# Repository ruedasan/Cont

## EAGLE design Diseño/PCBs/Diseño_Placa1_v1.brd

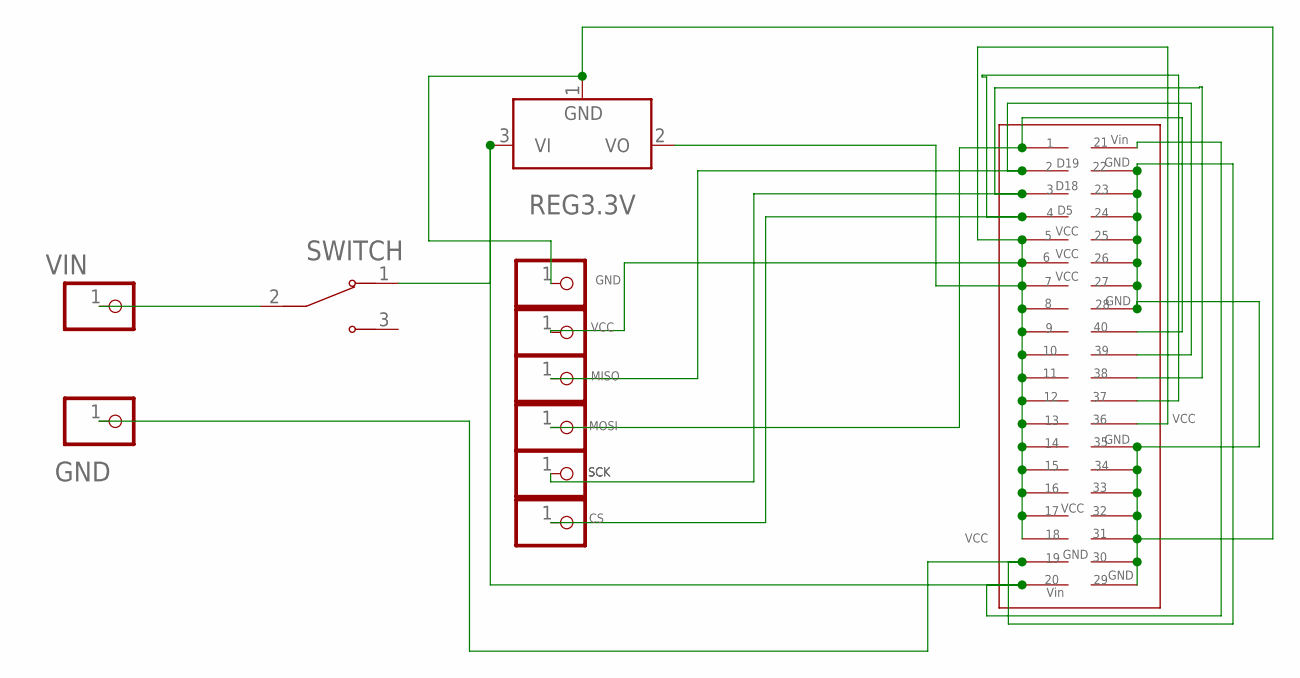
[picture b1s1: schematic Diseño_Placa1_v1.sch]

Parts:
GND: PINHD-1X1; 1X01
JP1: GND; 1X01
JP2: VCC; 1X01
JP3: MISO; 1X01
JP4: MOSI; 1X01
JP5: SCK; 1X01
JP6: CS; 1X01
REG3.3V: LD1117_TO220; TO220V
SWITCH: MINI-SPDT-SW; SW_MINI-SPDT-SW
U$1: PINHEADER
VIN: PINHD-1X1; 1X01

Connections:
unnamed: JP4.1, U$1.1, U$1.40
unnamed: SWITCH.2, VIN.1
unnamed: JP3.1, U$1.2, U$1.39
unnamed: JP5.1, U$1.3, U$1.38
unnamed: JP6.1, U$1.4, U$1.37
unnamed: GND.1, JP1.1, REG3.3V.1 (GND), U$1.19, U$1.22, U$1.23, U$1.24, U$1.25, U$1.26, U$1.27, U$1.28, U$1.29, U$1.30, U$1.31, U$1.32, U$1.33, U$1.34, U$1.35
unnamed: REG3.3V.3 (VI), SWITCH.1, U$1.20, U$1.21
unnamed: JP2.1, REG3.3V.2 (VO), U$1.5, U$1.6, U$1.7, U$1.8, U$1.9, U$1.10, U$1.11, U$1.12, U$1.13, U$1.14, U$1.15, U$1.16, U$1.17, U$1.18, U$1.36

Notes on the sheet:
D19
D18
GND
VCC
MISO
MOSI
SCK
Vin

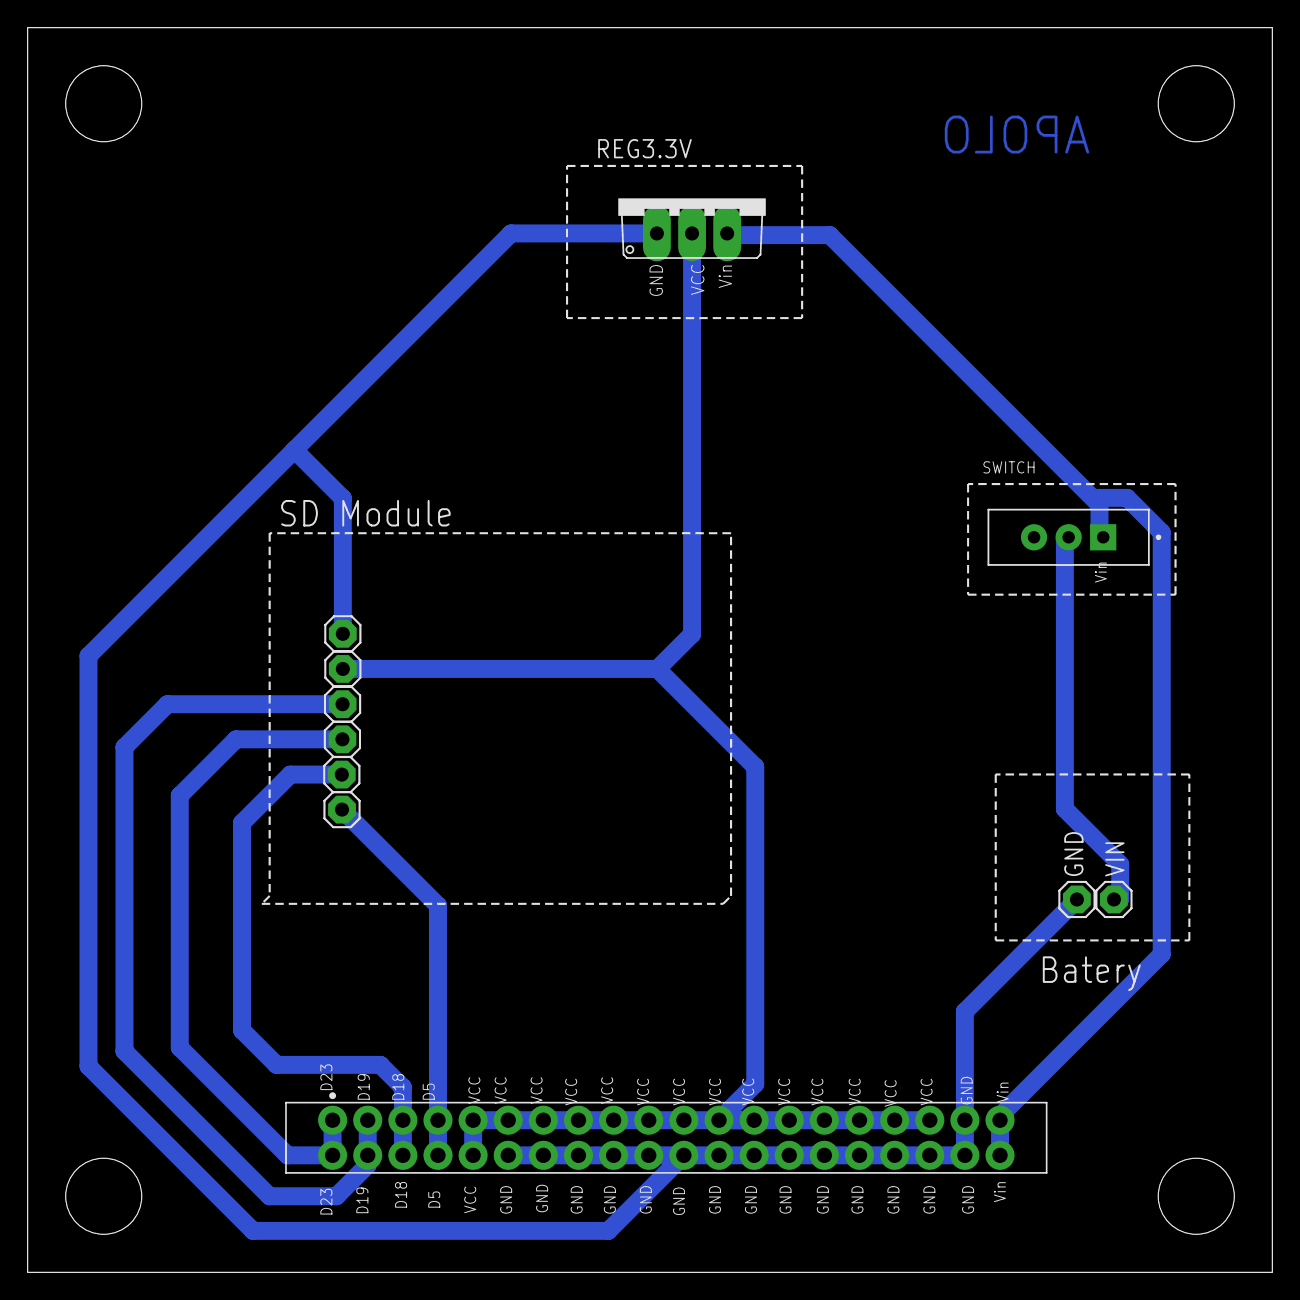
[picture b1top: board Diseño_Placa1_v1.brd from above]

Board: 2 copper layers, 90.0 x 90.0 mm, 11 parts (0 on the bottom side), 8 nets.

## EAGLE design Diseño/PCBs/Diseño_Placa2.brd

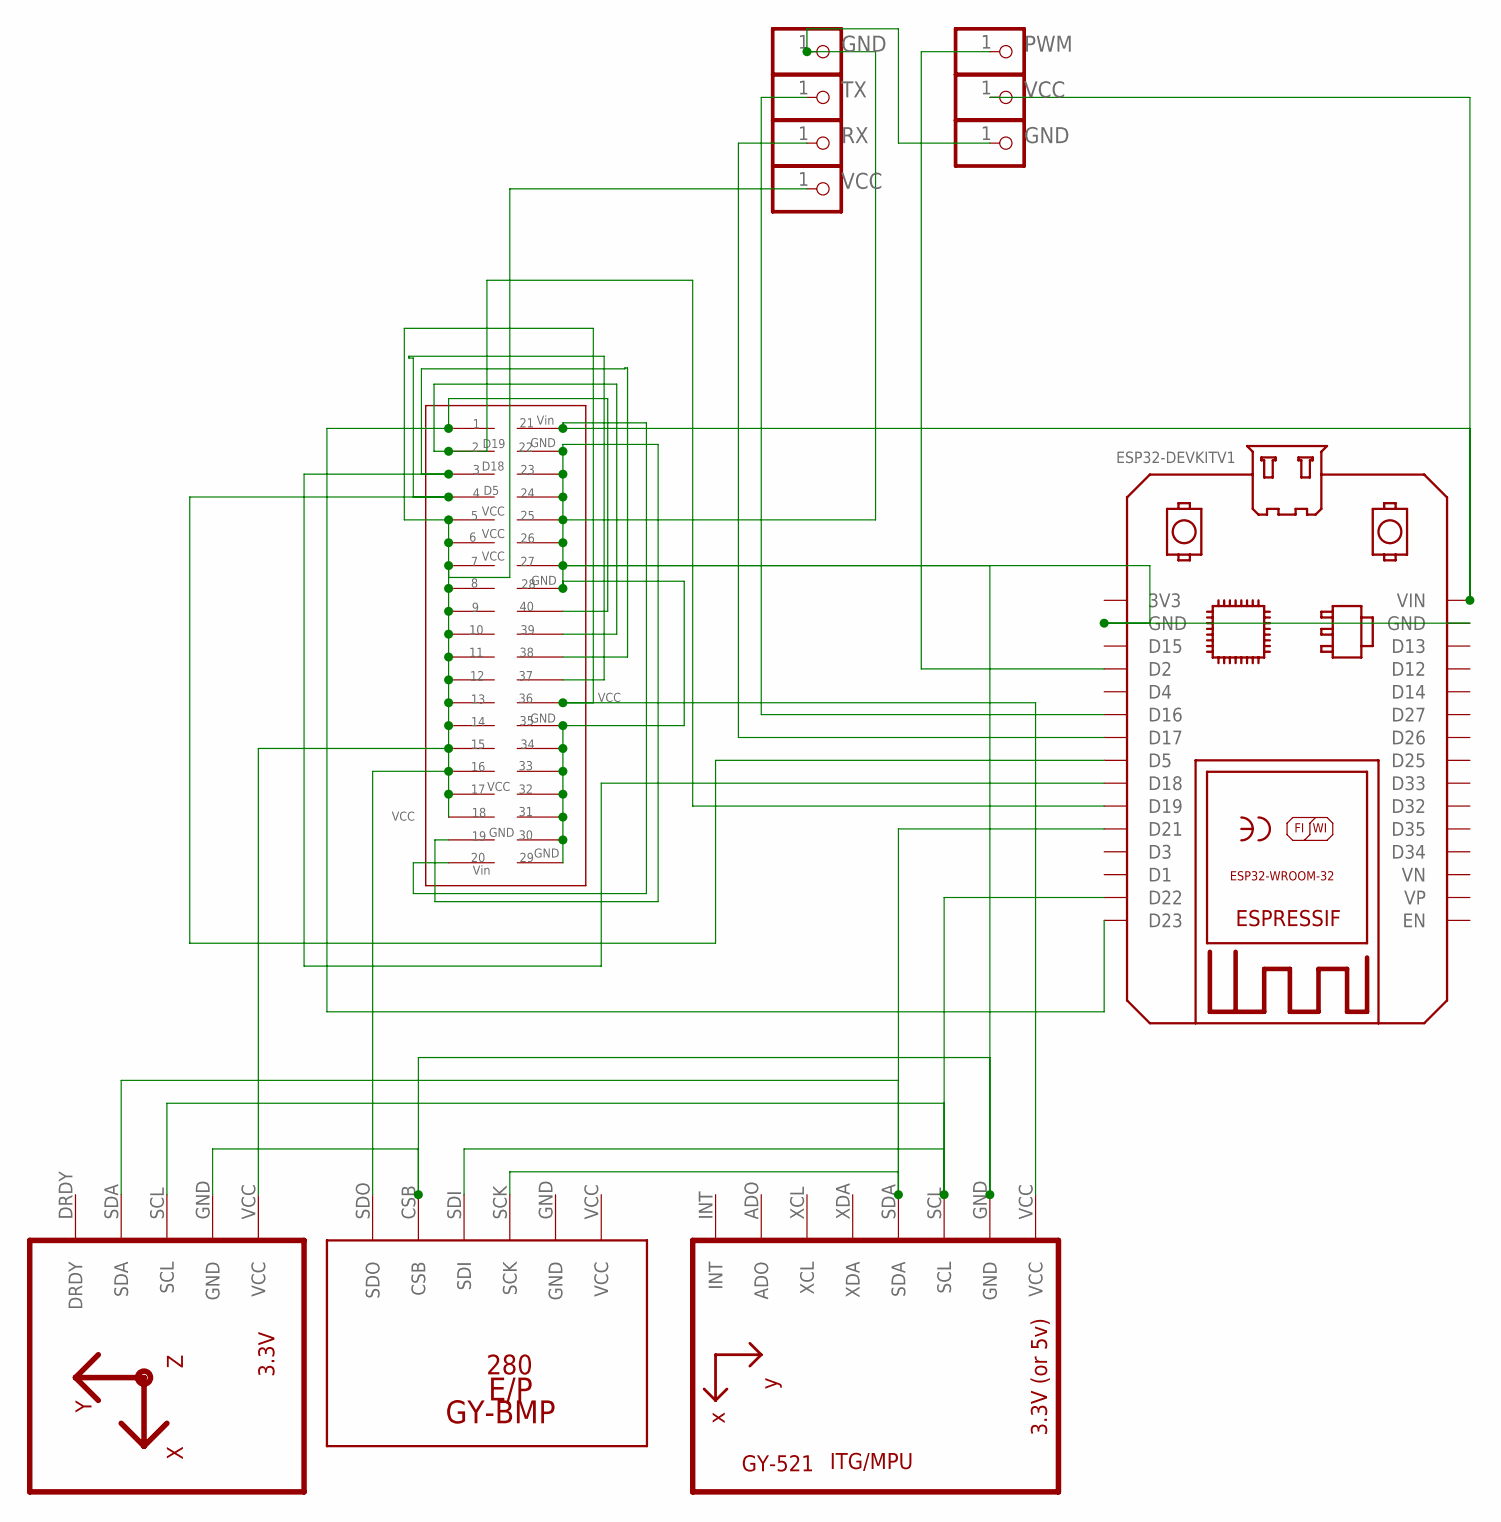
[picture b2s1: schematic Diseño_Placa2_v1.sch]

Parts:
3.3V: PWM; 1X01
3.3V3: GND; 1X01
3.3V4: VCC; 1X01
BOARD1: ESP32DEVKITV1; ESP32-DEVKITV1
GND: VCC; 1X01
GND3: TX; 1X01
GY-271: HMC5883LGY-271; GY-271
PWM: GND; 1X01
PWM3: RX; 1X01
U1: GY-521MPU6050; GY-521
U$1: GY-BPM280; GY-BMP280-FOOTPRINT
U$3: PINHEADER

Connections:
GND: 3.3V3.1, BOARD1.GND, BOARD1.GND@1 (GND), GY-271.GND, PWM.1, U1.GND, U$1.CSB, U$3.19, U$3.22, U$3.23, U$3.24, U$3.25, U$3.26, U$3.27, U$3.28, U$3.29, U$3.30, U$3.31, U$3.32, U$3.33, U$3.34, U$3.35
unnamed: BOARD1.D17, PWM3.1
unnamed: BOARD1.D16, GND3.1
unnamed: 3.3V.1, BOARD1.D2
unnamed: BOARD1.D22, GY-271.SCL, U1.SCL, U$1.SDI
unnamed: BOARD1.D21, GY-271.SDA, U1.SDA, U$1.SCK
unnamed: BOARD1.D23, U$3.1, U$3.40
unnamed: BOARD1.D19, U$3.2, U$3.39
unnamed: BOARD1.D18, U$3.3, U$3.38
unnamed: BOARD1.D5, U$3.4, U$3.37
unnamed: BOARD1.VIN, GND.1, U$3.20, U$3.21
unnamed: 3.3V4.1, GY-271.VCC, U1.VCC, U$1.SDO, U$3.5, U$3.6, U$3.7, U$3.8, U$3.9, U$3.10, U$3.11, U$3.12, U$3.13, U$3.14, U$3.15, U$3.16, U$3.17, U$3.18, U$3.36

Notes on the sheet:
D19
D18
VCC
Vin
GND

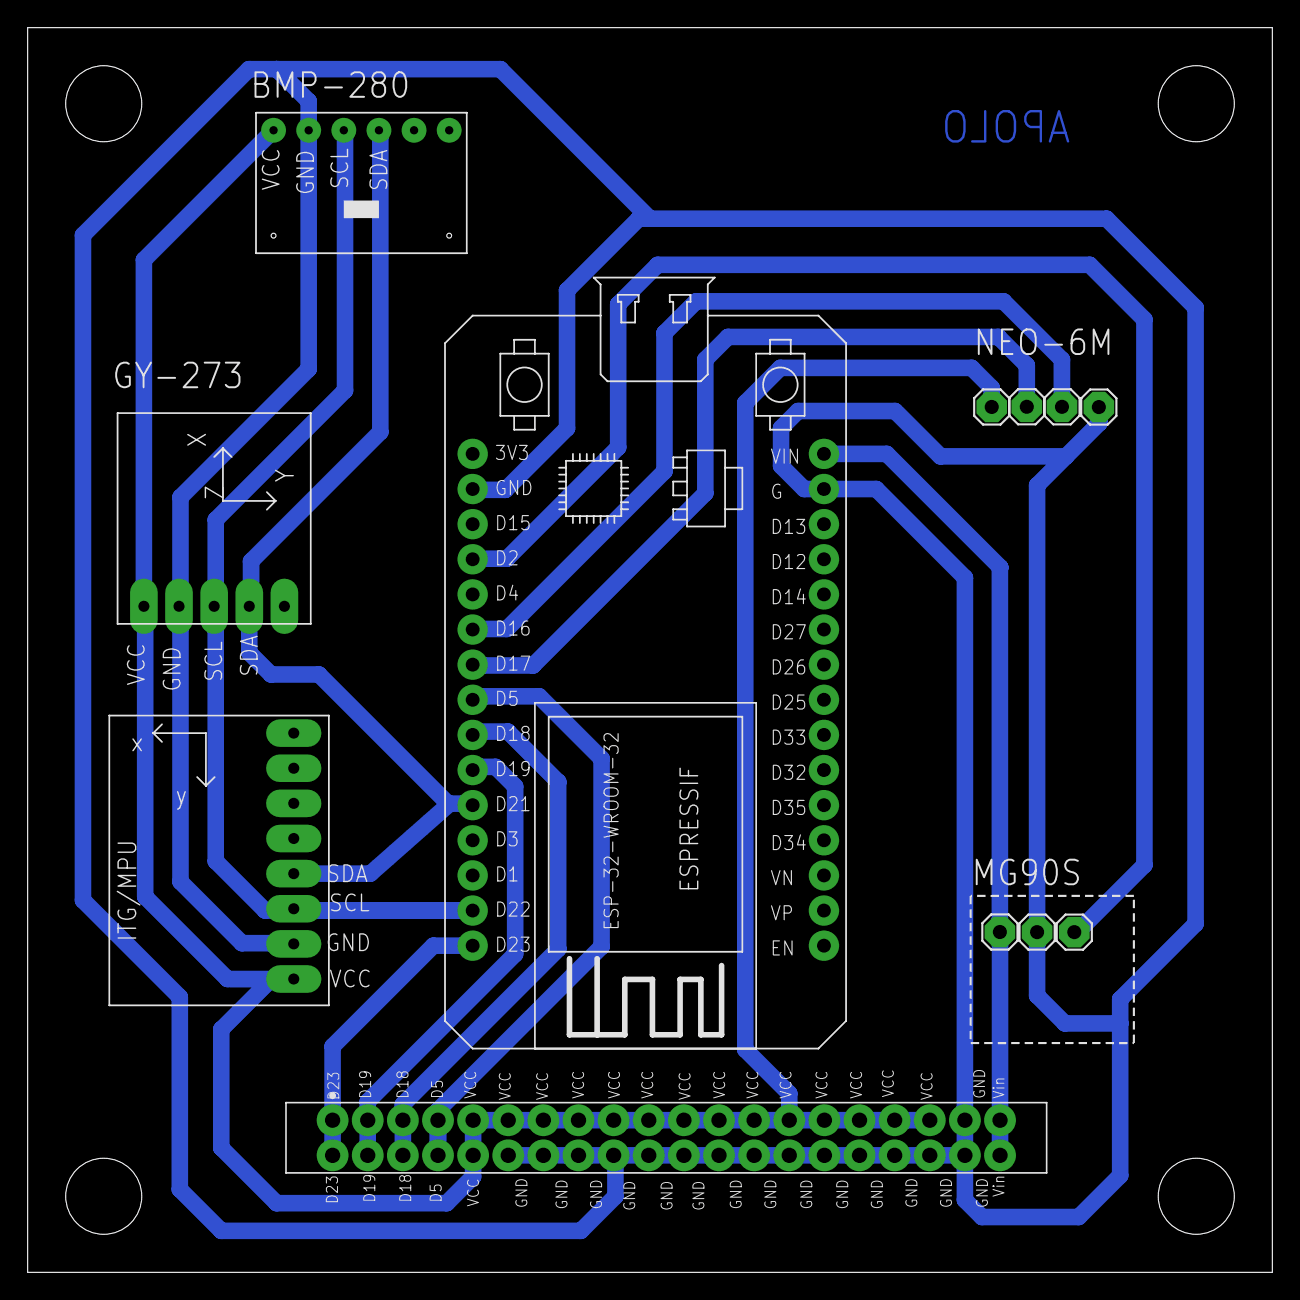
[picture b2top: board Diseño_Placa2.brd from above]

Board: 2 copper layers, 90.0 x 90.0 mm, 12 parts (0 on the bottom side), 12 nets.

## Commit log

2023-11-17 Create GPS
2023-11-17 Create BMP
2023-11-17 Create Funcional
2023-11-17 Create prueba
2023-11-17 Create Hola
2023-12-11 Create Completo
2023-12-11 Create Codigos
2023-12-11 Create df
2023-12-11 Update Completo
2023-12-12 Create ldnfsdn
2023-12-12 Create dwjfn
2023-12-12 Create kj
2023-12-12 Create kn
2023-12-12 Create Esquematico
2023-12-12 Create dsf
